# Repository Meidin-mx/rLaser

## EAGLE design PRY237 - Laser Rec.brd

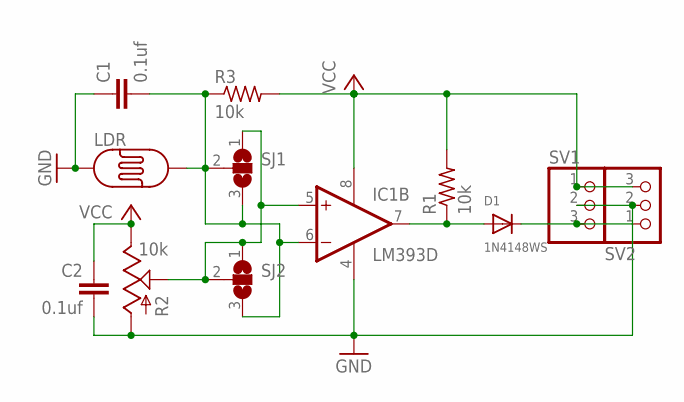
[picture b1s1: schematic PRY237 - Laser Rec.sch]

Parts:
C1, C2: 0.1uf; C0805
D1: 1N4148WS; SOD-323F
IC1: LM393D; SO08
LDR: PHOTOCELLPTH; PHOTOCELL
R1, R3: 10k; M0805
R2: 10k; CT6
SJ1, SJ2: SJ2W; SJ_2
SV1, SV2: PINHD-1X3; 1X03

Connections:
GND: C1.1, C2.2, IC1.4 (V-), LDR.1, R2.A, SV1.2, SV2.2
unnamed: IC1.5 (+IN), R2.S, SJ1.1, SJ2.1, SJ2.2
unnamed: D1.C, SV1.3, SV2.1
unnamed: D1.A, IC1.7 (OUT), R1.1
unnamed: C1.2, IC1.6 (-IN), LDR.2, R3.1, SJ1.2, SJ1.3, SJ2.3
VCC: C2.1, IC1.8 (V+), R1.2, R2.E, R3.2, SV1.1, SV2.3

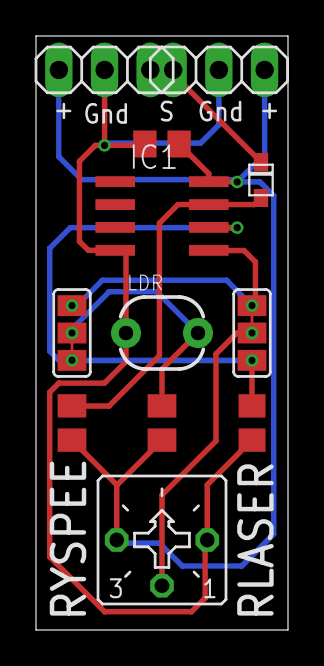
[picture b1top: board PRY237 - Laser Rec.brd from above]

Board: 2 copper layers, 14.0 x 33.0 mm, 12 parts (0 on the bottom side), 6 nets.

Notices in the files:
parts and their libraries:
SparkFun-Sensors: Licensing: Creative Commons ShareAlike 4.0 International - https://creativecommons.org/licenses/by-sa/4.0
